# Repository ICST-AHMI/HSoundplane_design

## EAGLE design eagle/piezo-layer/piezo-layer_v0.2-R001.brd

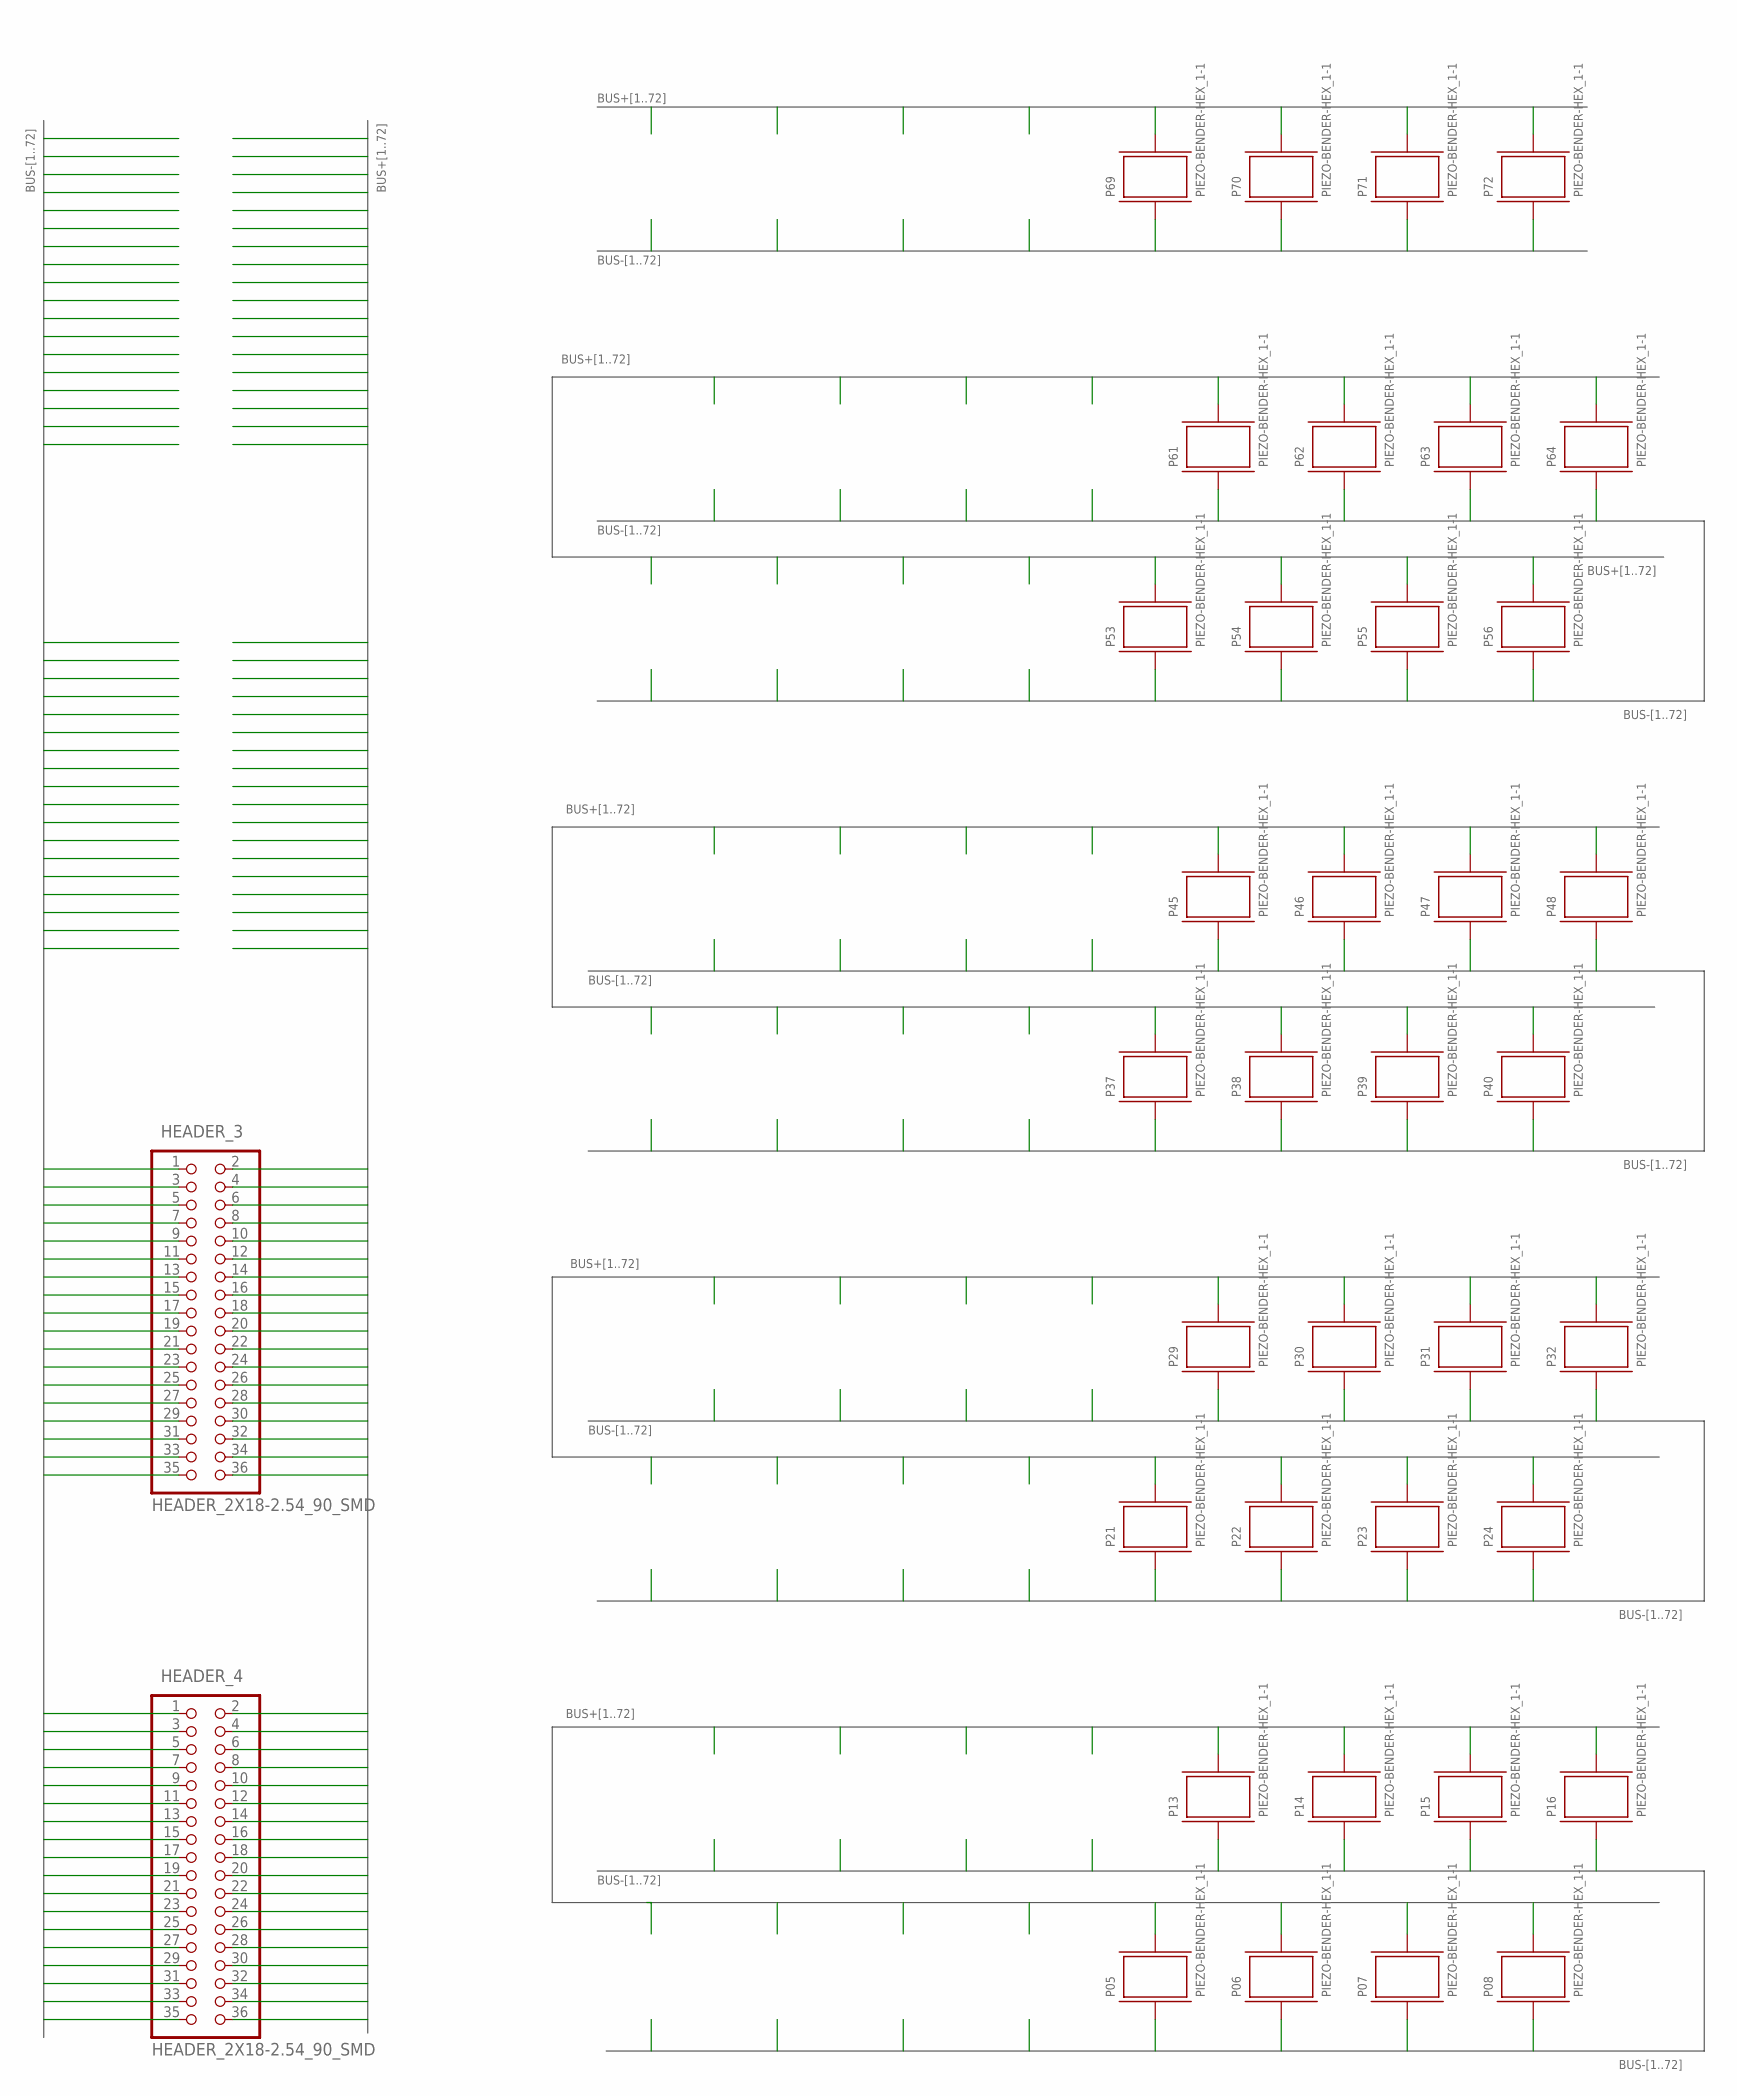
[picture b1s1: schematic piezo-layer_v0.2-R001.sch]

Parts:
HEADER_3, HEADER_4: HEADER_2X18-2.54_90_SMD; 2X18_2.54_90_SMD
P05, P06, P07, P08, P13, P14, P15, P16, P21, P22, P23, P24, P29, P30, P31, P32, P37, P38, P39, P40, P45, P46, P47, P48, P53, P54, P55, P56, P61, P62, P63, P64, P69, P70, P71, P72: PIEZO-BENDER-HEX_1-1; PIEZO-BENDER-HEX_16MM_1+_1-

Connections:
BUS+5: HEADER_3.18, P05.TIP1 (+_1)
BUS+6: HEADER_3.36, P06.TIP1 (+_1)
BUS+7: HEADER_4.18, P07.TIP1 (+_1)
BUS+8: HEADER_4.36, P08.TIP1 (+_1)
BUS+13: HEADER_3.16, P13.TIP1 (+_1)
BUS+14: HEADER_3.34, P14.TIP1 (+_1)
BUS+15: HEADER_4.16, P15.TIP1 (+_1)
BUS+16: HEADER_4.34, P16.TIP1 (+_1)
BUS+21: HEADER_3.14, P21.TIP1 (+_1)
BUS+22: HEADER_3.32, P22.TIP1 (+_1)
BUS+23: HEADER_4.14, P23.TIP1 (+_1)
BUS+24: HEADER_4.32, P24.TIP1 (+_1)
BUS+29: HEADER_3.12, P29.TIP1 (+_1)
BUS+30: HEADER_3.30, P30.TIP1 (+_1)
BUS+31: HEADER_4.12, P31.TIP1 (+_1)
BUS+32: HEADER_4.30, P32.TIP1 (+_1)
BUS+37: HEADER_3.10, P37.TIP1 (+_1)
BUS+38: HEADER_3.28, P38.TIP1 (+_1)
BUS+39: HEADER_4.10, P39.TIP1 (+_1)
BUS+40: HEADER_4.28, P40.TIP1 (+_1)
BUS+45: HEADER_3.8, P45.TIP1 (+_1)
BUS+46: HEADER_3.26, P46.TIP1 (+_1)
BUS+47: HEADER_4.8, P47.TIP1 (+_1)
BUS+48: HEADER_4.26, P48.TIP1 (+_1)
BUS+53: HEADER_3.6, P53.TIP1 (+_1)
BUS+54: HEADER_3.24, P54.TIP1 (+_1)
BUS+55: HEADER_4.6, P55.TIP1 (+_1)
BUS+56: HEADER_4.24, P56.TIP1 (+_1)
BUS+61: HEADER_3.4, P61.TIP1 (+_1)
BUS+62: HEADER_3.22, P62.TIP1 (+_1)
BUS+63: HEADER_4.4, P63.TIP1 (+_1)
BUS+64: HEADER_4.22, P64.TIP1 (+_1)
BUS+69: HEADER_3.2, P69.TIP1 (+_1)
BUS+70: HEADER_3.20, P70.TIP1 (+_1)
BUS+71: HEADER_4.2, P71.TIP1 (+_1)
BUS+72: HEADER_4.20, P72.TIP1 (+_1)
BUS-5: HEADER_3.17, P05.PAD1 (-_1)
BUS-6: HEADER_3.35, P06.PAD1 (-_1)
BUS-7: HEADER_4.17, P07.PAD1 (-_1)
BUS-8: HEADER_4.35, P08.PAD1 (-_1)
BUS-13: HEADER_3.15, P13.PAD1 (-_1)
BUS-14: HEADER_3.33, P14.PAD1 (-_1)
BUS-15: HEADER_4.15, P15.PAD1 (-_1)
BUS-16: HEADER_4.33, P16.PAD1 (-_1)
BUS-21: HEADER_3.13, P21.PAD1 (-_1)
BUS-22: HEADER_3.31, P22.PAD1 (-_1)
BUS-23: HEADER_4.13, P23.PAD1 (-_1)
BUS-24: HEADER_4.31, P24.PAD1 (-_1)
BUS-29: HEADER_3.11, P29.PAD1 (-_1)
BUS-30: HEADER_3.29, P30.PAD1 (-_1)
BUS-31: HEADER_4.11, P31.PAD1 (-_1)
BUS-32: HEADER_4.29, P32.PAD1 (-_1)
BUS-37: HEADER_3.9, P37.PAD1 (-_1)
BUS-38: HEADER_3.27, P38.PAD1 (-_1)
BUS-39: HEADER_4.9, P39.PAD1 (-_1)
BUS-40: HEADER_4.27, P40.PAD1 (-_1)
BUS-45: HEADER_3.7, P45.PAD1 (-_1)
BUS-46: HEADER_3.25, P46.PAD1 (-_1)
BUS-47: HEADER_4.7, P47.PAD1 (-_1)
BUS-48: HEADER_4.25, P48.PAD1 (-_1)
BUS-53: HEADER_3.5, P53.PAD1 (-_1)
BUS-54: HEADER_3.23, P54.PAD1 (-_1)
BUS-55: HEADER_4.5, P55.PAD1 (-_1)
BUS-56: HEADER_4.23, P56.PAD1 (-_1)
BUS-61: HEADER_3.3, P61.PAD1 (-_1)
BUS-62: HEADER_3.21, P62.PAD1 (-_1)
BUS-63: HEADER_4.3, P63.PAD1 (-_1)
BUS-64: HEADER_4.21, P64.PAD1 (-_1)
BUS-69: HEADER_3.1, P69.PAD1 (-_1)
BUS-70: HEADER_3.19, P70.PAD1 (-_1)
BUS-71: HEADER_4.1, P71.PAD1 (-_1)
BUS-72: HEADER_4.19, P72.PAD1 (-_1)

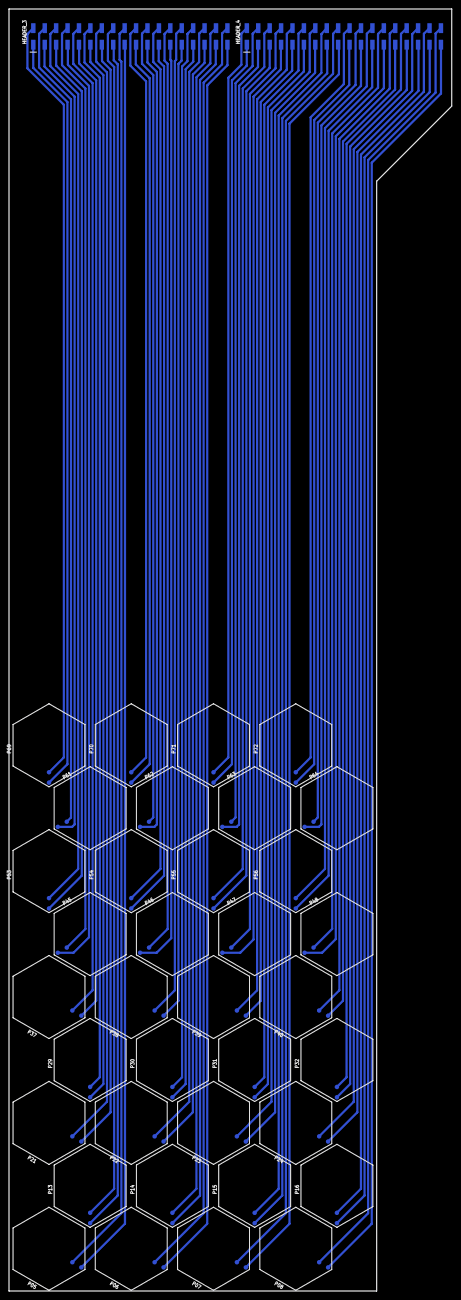
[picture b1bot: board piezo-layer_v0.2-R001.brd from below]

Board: 2 copper layers, 98.5 x 285.2 mm, 38 parts (38 on the bottom side), 72 nets.

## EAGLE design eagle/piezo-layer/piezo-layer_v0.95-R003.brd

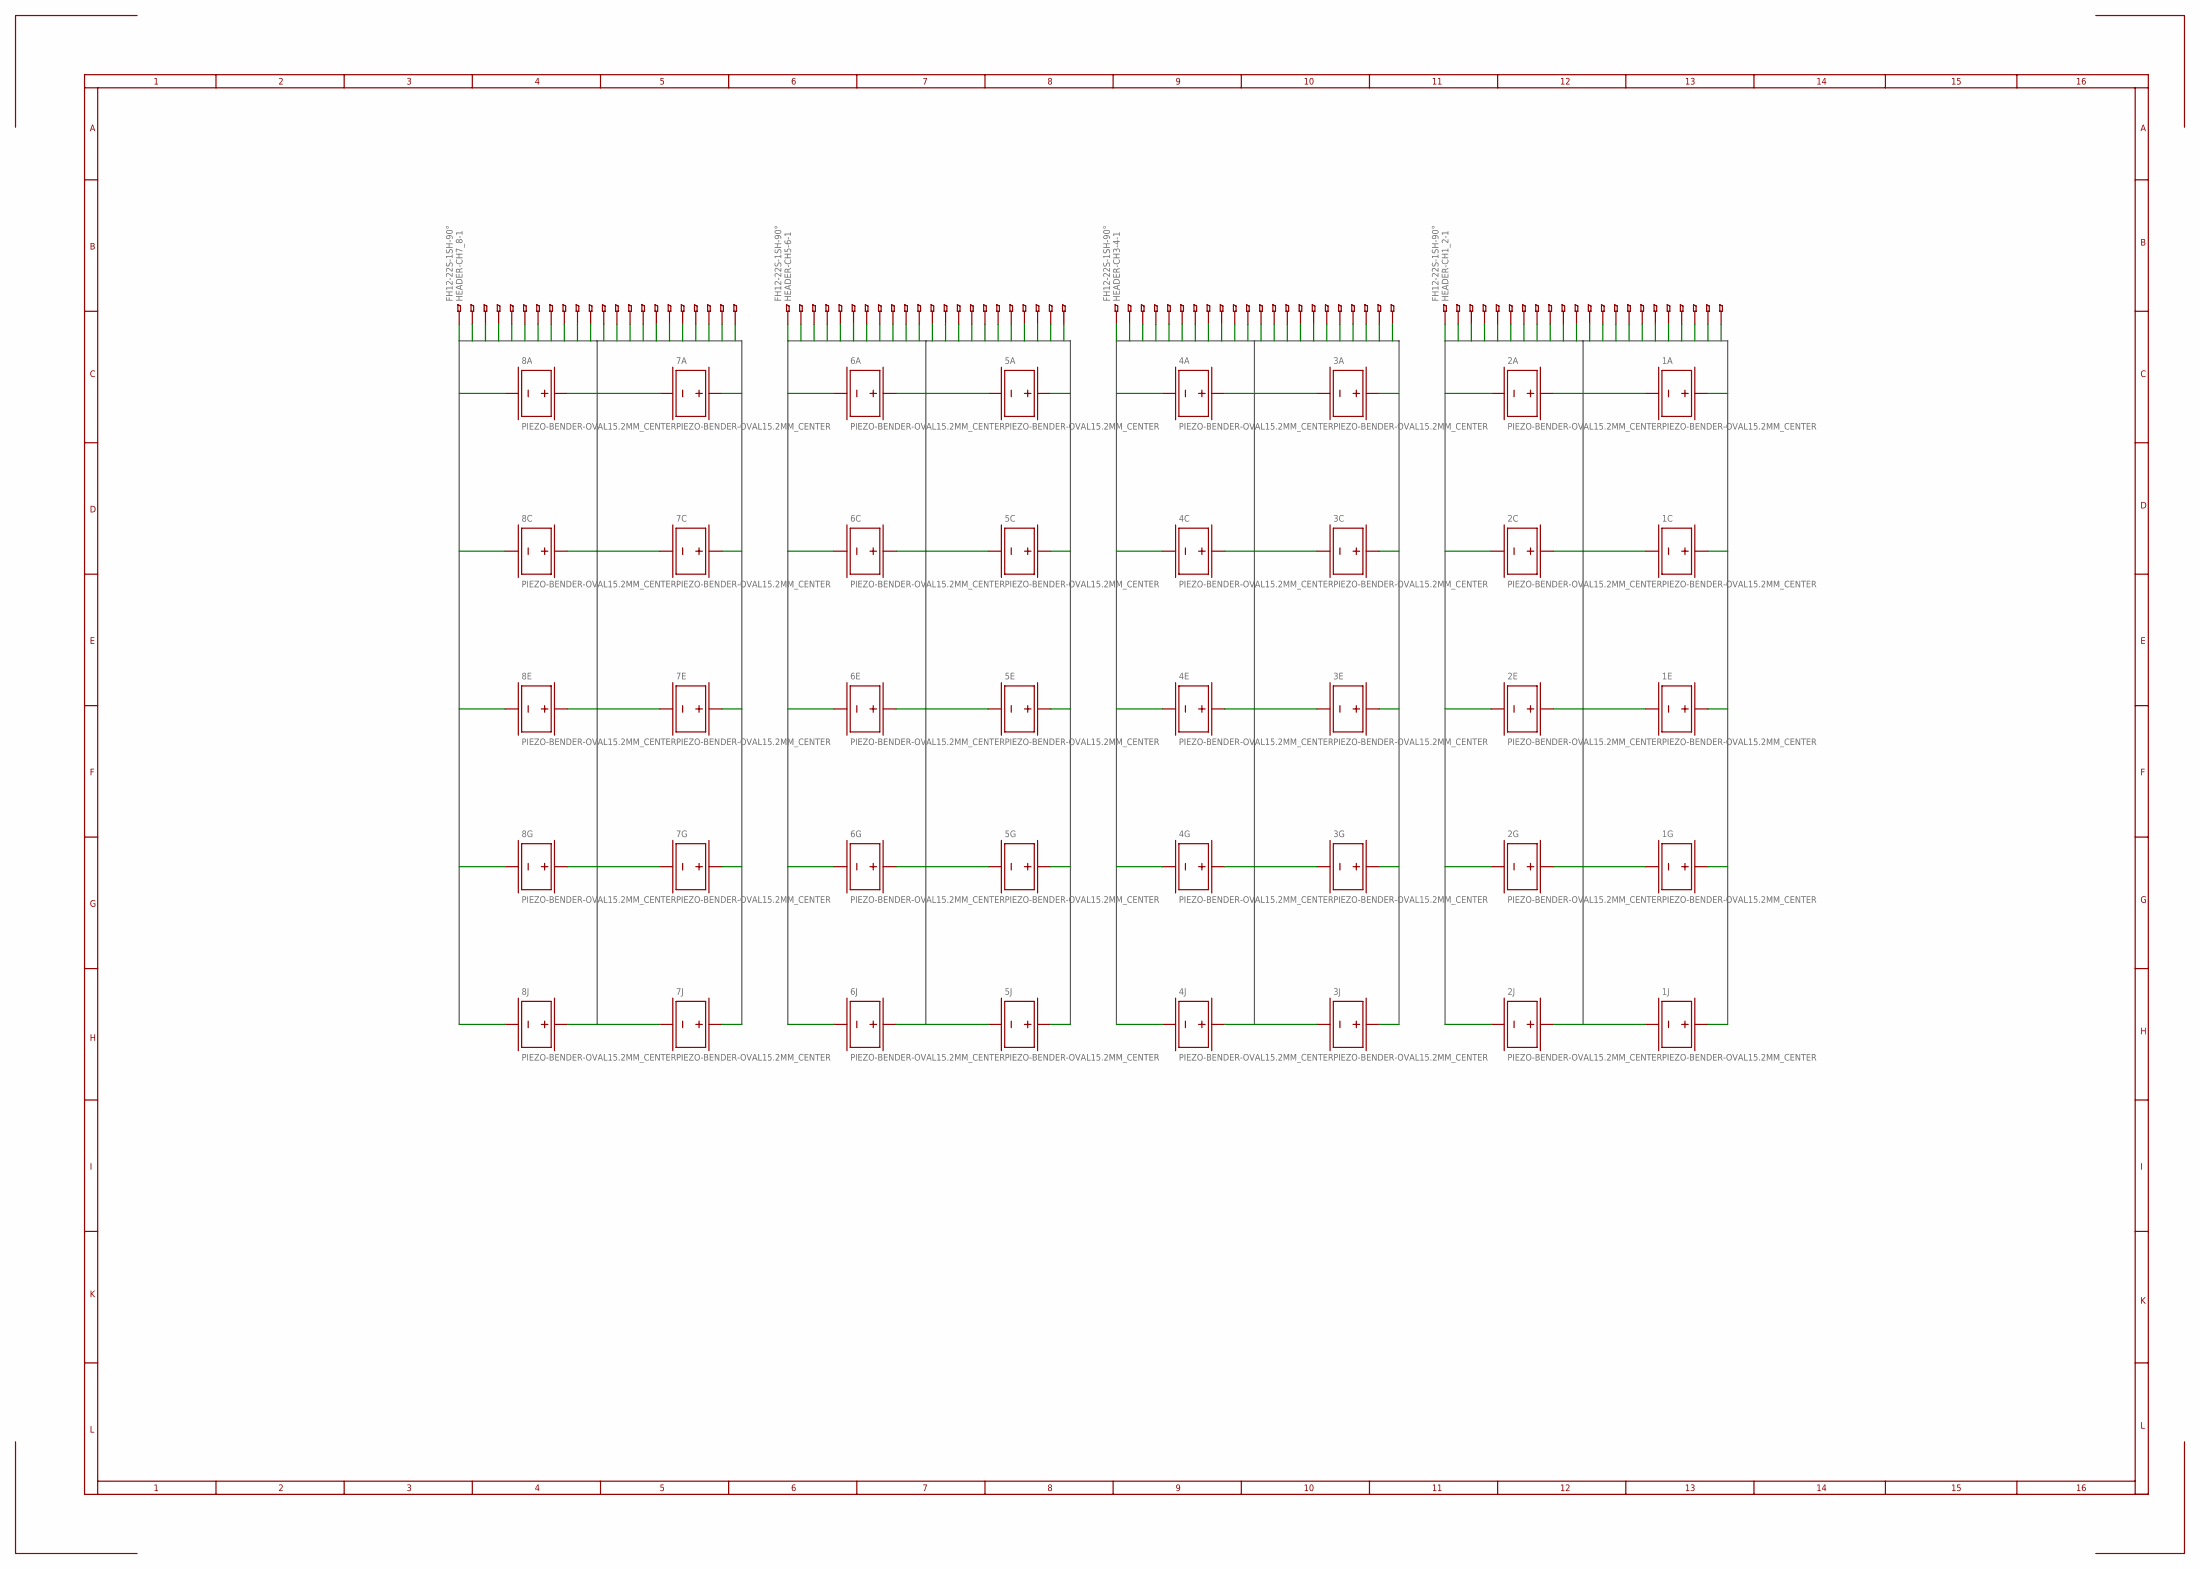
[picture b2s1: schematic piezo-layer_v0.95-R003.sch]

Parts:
1A, 1C, 1E, 1G, 1J, 2A, 2C, 2E, 2G, 2J, 3A, 3C, 3E, 3G, 3J, 4A, 4C, 4E, 4G, 4J, 5A, 5C, 5E, 5G, 5J, 6A, 6C, 6E, 6G, 6J, 7A, 7C, 7E, 7G, 7J, 8A, 8C, 8E, 8G, 8J: PIEZO-BENDER-OVAL15.2MM_CENTER; PIEZO-BENDER-OVAL_15.2MM_BIGPADS_CENTER
HEADER-CH1_2, HEADER-CH3-4, HEADER-CH5-6, HEADER-CH7_8: FH12-22S-1SH-90°; FH12-22S-1SH

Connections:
BUS1: 1J.TOP (+_1), HEADER-CH1_2.22
BUS2: HEADER-CH1_2.21
BUS3: 1E.TOP (+_1), HEADER-CH1_2.20
BUS4: HEADER-CH1_2.19
BUS5: 1A.BOTTOM (-_1), 1C.BOTTOM (-_1), 1E.BOTTOM (-_1), 1G.BOTTOM (-_1), 1J.BOTTOM (-_1), HEADER-CH1_2.12, HEADER-CH1_2.18
BUS6: 1A.TOP (+_1), HEADER-CH1_2.17
BUS7: HEADER-CH1_2.16
BUS8: 1C.TOP (+_1), HEADER-CH1_2.15
BUS9: HEADER-CH1_2.14
BUS10: 1G.TOP (+_1), HEADER-CH1_2.13
BUS11: 2J.TOP (+_1), HEADER-CH1_2.11
BUS12: HEADER-CH1_2.10
BUS13: 2E.TOP (+_1), HEADER-CH1_2.9
BUS14: HEADER-CH1_2.8
BUS15: 2A.BOTTOM (-_1), 2C.BOTTOM (-_1), 2E.BOTTOM (-_1), 2G.BOTTOM (-_1), 2J.BOTTOM (-_1), HEADER-CH1_2.1, HEADER-CH1_2.7
BUS16: 2A.TOP (+_1), HEADER-CH1_2.6
BUS17: HEADER-CH1_2.5
BUS18: 2C.TOP (+_1), HEADER-CH1_2.4
BUS19: HEADER-CH1_2.3
BUS20: 2G.TOP (+_1), HEADER-CH1_2.2
BUS21: 3J.TOP (+_1), HEADER-CH3-4.22
BUS22: HEADER-CH3-4.21
BUS23: 3E.TOP (+_1), HEADER-CH3-4.20
BUS24: HEADER-CH3-4.19
BUS25: 3A.BOTTOM (-_1), 3C.BOTTOM (-_1), 3E.BOTTOM (-_1), 3G.BOTTOM (-_1), 3J.BOTTOM (-_1), HEADER-CH3-4.12, HEADER-CH3-4.18
BUS26: 3A.TOP (+_1), HEADER-CH3-4.17
BUS27: HEADER-CH3-4.16
BUS28: 3C.TOP (+_1), HEADER-CH3-4.15
BUS29: HEADER-CH3-4.14
BUS30: 3G.TOP (+_1), HEADER-CH3-4.13
BUS31: 4J.TOP (+_1), HEADER-CH3-4.11
BUS32: HEADER-CH3-4.10
BUS33: 4E.TOP (+_1), HEADER-CH3-4.9
BUS34: HEADER-CH3-4.8
BUS35: 4A.BOTTOM (-_1), 4C.BOTTOM (-_1), 4E.BOTTOM (-_1), 4G.BOTTOM (-_1), 4J.BOTTOM (-_1), HEADER-CH3-4.1, HEADER-CH3-4.7
BUS36: 4A.TOP (+_1), HEADER-CH3-4.6
BUS37: HEADER-CH3-4.5
BUS38: 4C.TOP (+_1), HEADER-CH3-4.4
BUS39: HEADER-CH3-4.3
BUS40: 4G.TOP (+_1), HEADER-CH3-4.2
BUS41: 5J.TOP (+_1), HEADER-CH5-6.22
BUS42: HEADER-CH5-6.21
BUS43: 5E.TOP (+_1), HEADER-CH5-6.20
BUS44: HEADER-CH5-6.19
BUS45: 5A.BOTTOM (-_1), 5C.BOTTOM (-_1), 5E.BOTTOM (-_1), 5G.BOTTOM (-_1), 5J.BOTTOM (-_1), HEADER-CH5-6.12, HEADER-CH5-6.18
BUS46: 5A.TOP (+_1), HEADER-CH5-6.17
BUS47: HEADER-CH5-6.16
BUS48: 5C.TOP (+_1), HEADER-CH5-6.15
BUS49: HEADER-CH5-6.14
BUS50: 5G.TOP (+_1), HEADER-CH5-6.13
BUS51: 6J.TOP (+_1), HEADER-CH5-6.11
BUS52: HEADER-CH5-6.10
BUS53: 6E.TOP (+_1), HEADER-CH5-6.9
BUS54: HEADER-CH5-6.8
BUS55: 6A.BOTTOM (-_1), 6C.BOTTOM (-_1), 6E.BOTTOM (-_1), 6G.BOTTOM (-_1), 6J.BOTTOM (-_1), HEADER-CH5-6.1, HEADER-CH5-6.7
BUS56: 6A.TOP (+_1), HEADER-CH5-6.6
BUS57: HEADER-CH5-6.5
BUS58: 6C.TOP (+_1), HEADER-CH5-6.4
BUS59: HEADER-CH5-6.3
BUS60: 6G.TOP (+_1), HEADER-CH5-6.2
BUS61: 7J.TOP (+_1), HEADER-CH7_8.22
BUS62: HEADER-CH7_8.21
BUS63: 7E.TOP (+_1), HEADER-CH7_8.20
BUS64: HEADER-CH7_8.19
BUS65: 7A.BOTTOM (-_1), 7C.BOTTOM (-_1), 7E.BOTTOM (-_1), 7G.BOTTOM (-_1), 7J.BOTTOM (-_1), HEADER-CH7_8.12, HEADER-CH7_8.18
BUS66: 7A.TOP (+_1), HEADER-CH7_8.17
BUS67: HEADER-CH7_8.16
BUS68: 7C.TOP (+_1), HEADER-CH7_8.15
BUS69: HEADER-CH7_8.14
BUS70: 7G.TOP (+_1), HEADER-CH7_8.13
BUS71: 8J.TOP (+_1), HEADER-CH7_8.11
BUS72: HEADER-CH7_8.10
BUS73: 8E.TOP (+_1), HEADER-CH7_8.9
BUS74: HEADER-CH7_8.8
BUS75: 8A.BOTTOM (-_1), 8C.BOTTOM (-_1), 8E.BOTTOM (-_1), 8G.BOTTOM (-_1), 8J.BOTTOM (-_1), HEADER-CH7_8.1, HEADER-CH7_8.7
BUS76: 8A.TOP (+_1), HEADER-CH7_8.6
BUS77: HEADER-CH7_8.5
BUS78: 8C.TOP (+_1), HEADER-CH7_8.4
BUS79: HEADER-CH7_8.3
BUS80: 8G.TOP (+_1), HEADER-CH7_8.2

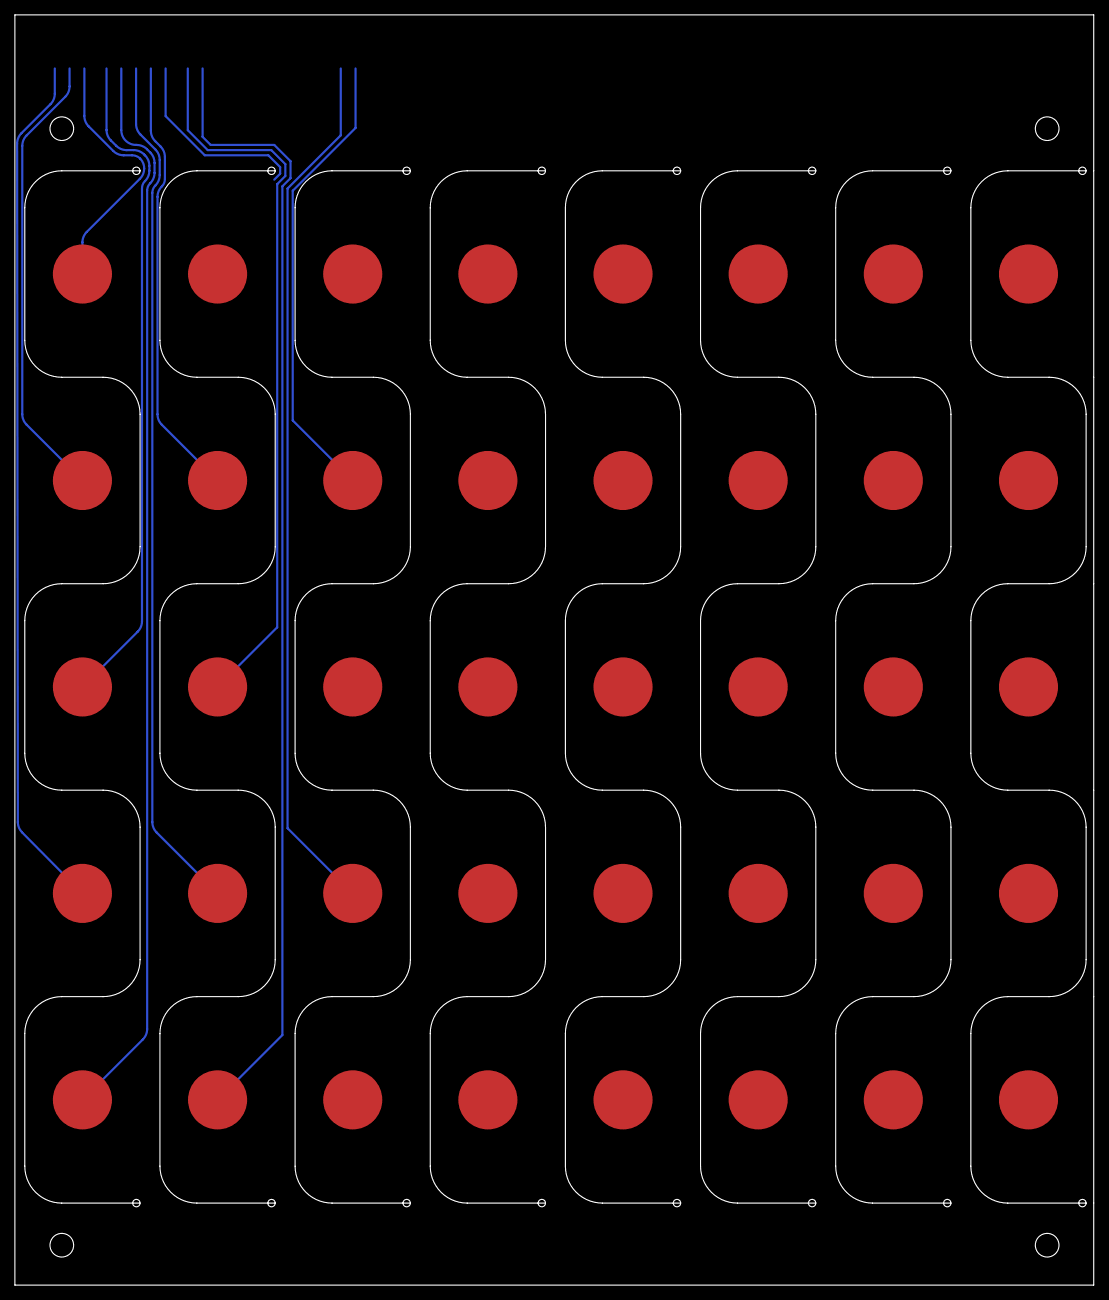
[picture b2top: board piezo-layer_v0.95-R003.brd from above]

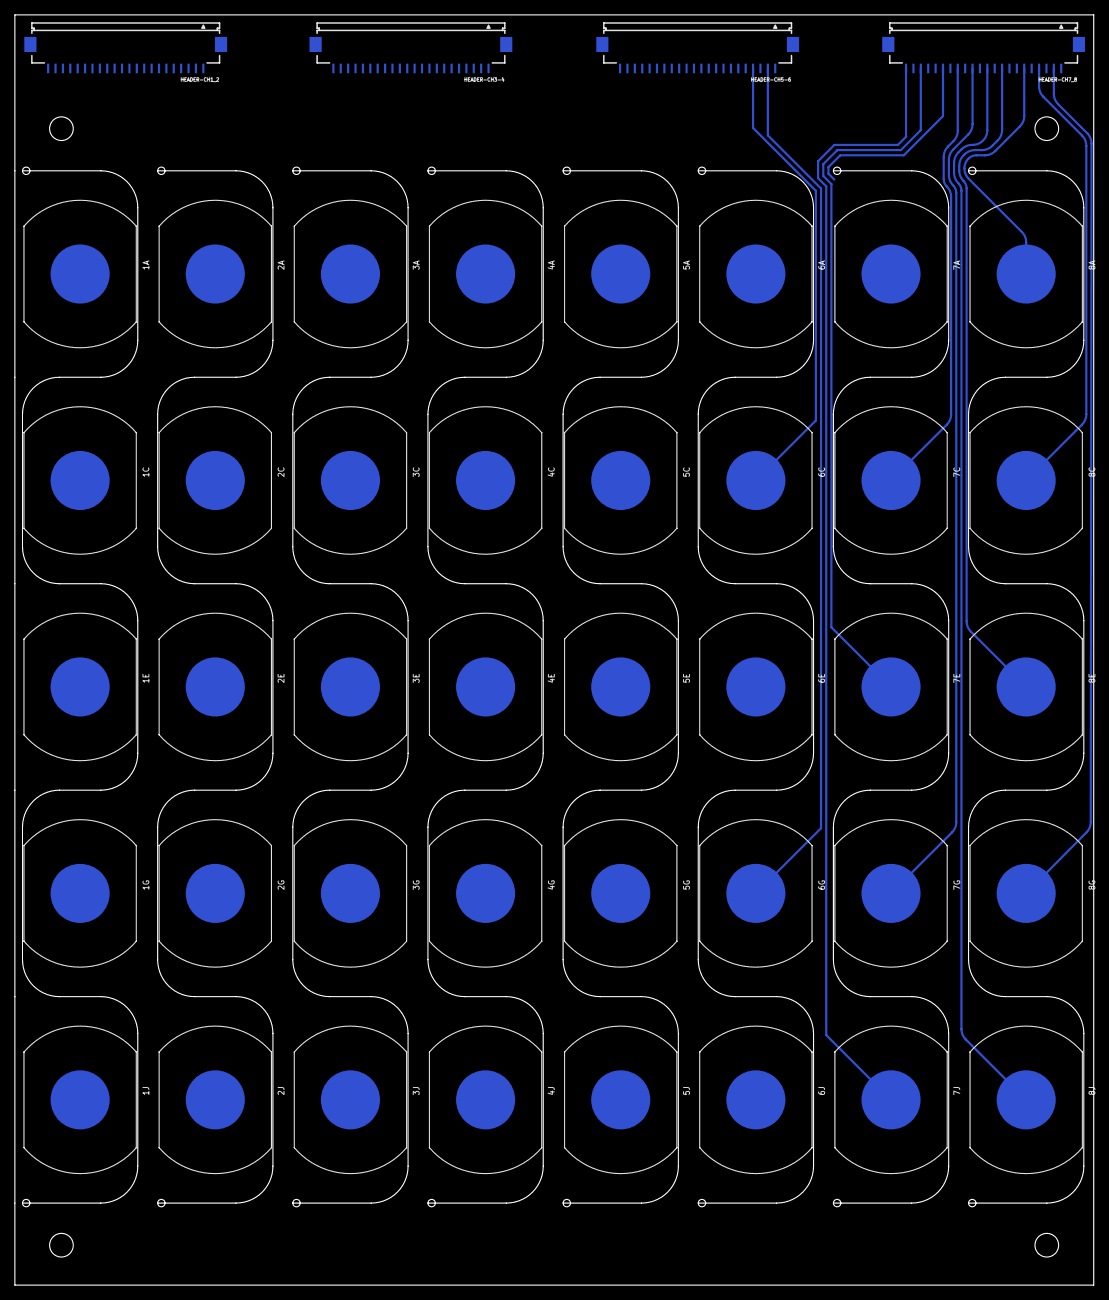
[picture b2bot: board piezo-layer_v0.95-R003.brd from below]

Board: 2 copper layers, 146.0 x 171.9 mm, 44 parts (44 on the bottom side), 48 nets.
